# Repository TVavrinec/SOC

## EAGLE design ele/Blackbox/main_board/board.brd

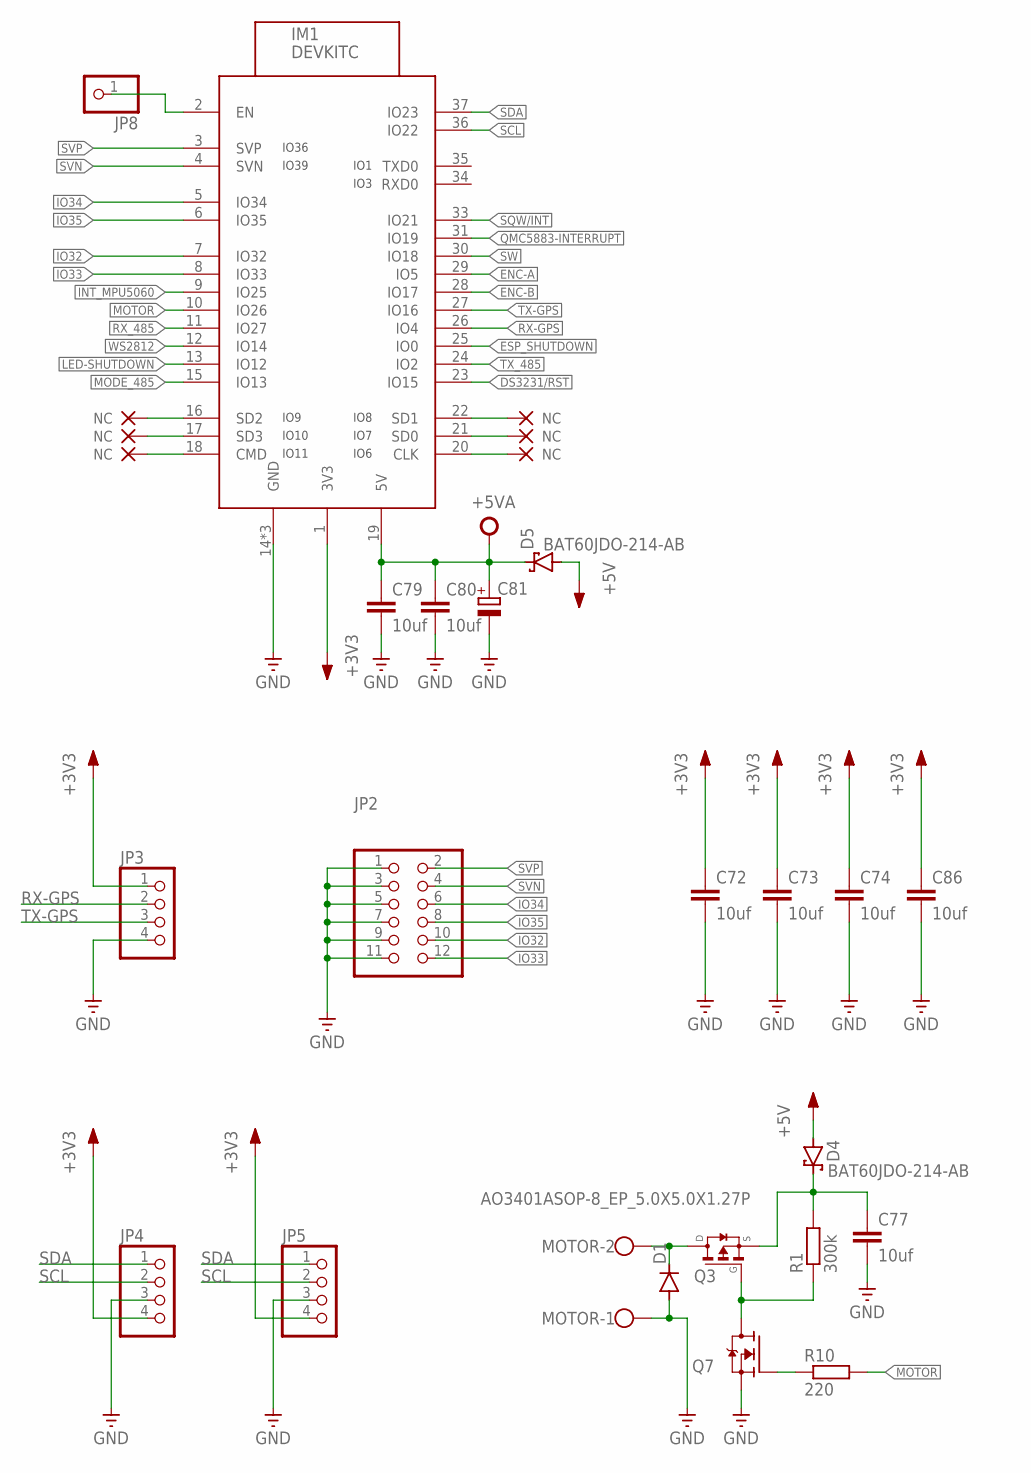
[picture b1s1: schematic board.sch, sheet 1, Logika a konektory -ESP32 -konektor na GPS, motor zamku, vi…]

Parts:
C72, C73, C74, C77, C79, C80, C86: 10uf; C0805
C81: CPOL-EU; E5-10,5-H
D1: DIODE-DO214BA; DO214BA
D4, D5: BAT60JDO-214-AB; DO214BA
IM1: DEVKITC
JP2: PINHD-2X6; 2X06
JP3, JP4, JP5: PINHD-1X4; 1X04
JP8: PINHD-1X1; 1X01
MOTOR: W237-102
Q3: AO3401ASOP-8_EP_5.0X5.0X1.27P; SOP-8_EP_5.0X5.0X1.27P
Q7: N-MOSFET-SOT23-GSD; SOT23
R1: 300k; R0402
R10: 220; R0402

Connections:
+3V3: C72.1, C73.1, C74.1, C86.1, IM1.1 (3V3), JP3.1, JP4.4, JP5.4; also elsewhere on the board
+5V: D4.A, D5.A; also elsewhere on the board
+5VA: C79.1, C80.1, C81.+, D5.C, IM1.19 (5V); also elsewhere on the board
DS3231/RST: IM1.23 (IO15); also elsewhere on the board
ENC-A: IM1.29 (IO5); also elsewhere on the board
ENC-B: IM1.28 (IO17); also elsewhere on the board
ESP_SHUTDOWN: IM1.25 (IO0); also elsewhere on the board
GND: C72.2, C73.2, C74.2, C77.2, C79.2, C80.2, C81.-, C86.2, D1.A, IM1.14 (GND), IM1.32 (GND), IM1.38 (GND), JP2.1, JP2.3, JP2.5, JP2.7, JP2.9, JP2.11, JP3.4, JP4.3, JP5.3, MOTOR.1, Q7.2 (S); also elsewhere on the board
INT_MPU5060: IM1.9 (IO25); also elsewhere on the board
IO9_NC: IM1.16 (SD2)
IO9_NC1: IM1.20 (CLK)
IO10_NC: IM1.17 (SD3)
IO10_NC1: IM1.21 (SD0)
IO11_NC: IM1.18 (CMD)
IO11_NC1: IM1.22 (SD1)
IO32: IM1.7 (IO32), JP2.10
IO33: IM1.8 (IO33), JP2.12
IO34: IM1.5 (IO34), JP2.6
IO35: IM1.6 (IO35), JP2.8
LED-SHUTDOWN: IM1.13 (IO12); also elsewhere on the board
MODE_485: IM1.15 (IO13); also elsewhere on the board
MOTOR: IM1.10 (IO26), R10.2
unnamed: IM1.2 (EN), JP8.1
unnamed: D1.C, MOTOR.2, Q3.5 (D), Q3.6 (D), Q3.7 (D), Q3.8 (D), Q3.9 (D)
unnamed: Q3.4 (G), Q7.3 (D), R1.1
unnamed: Q7.1 (G), R10.1
unnamed: C77.1, D4.C, Q3.1 (S), Q3.2 (S), Q3.3 (S), R1.2
QMC5883-INTERRUPT: IM1.31 (IO19); also elsewhere on the board
RX-GPS: IM1.26 (IO4), JP3.2
RX_485: IM1.11 (IO27); also elsewhere on the board
SCL: IM1.36 (IO22), JP4.2, JP5.2; also elsewhere on the board
SDA: IM1.37 (IO23), JP4.1, JP5.1; also elsewhere on the board
SQW/INT: IM1.33 (IO21); also elsewhere on the board
SVN: IM1.4 (SVN), JP2.4
SVP: IM1.3 (SVP), JP2.2
SW: IM1.30 (IO18); also elsewhere on the board
TX-GPS: IM1.27 (IO16), JP3.3
TX_485: IM1.24 (IO2); also elsewhere on the board
WS2812: IM1.12 (IO14); also elsewhere on the board

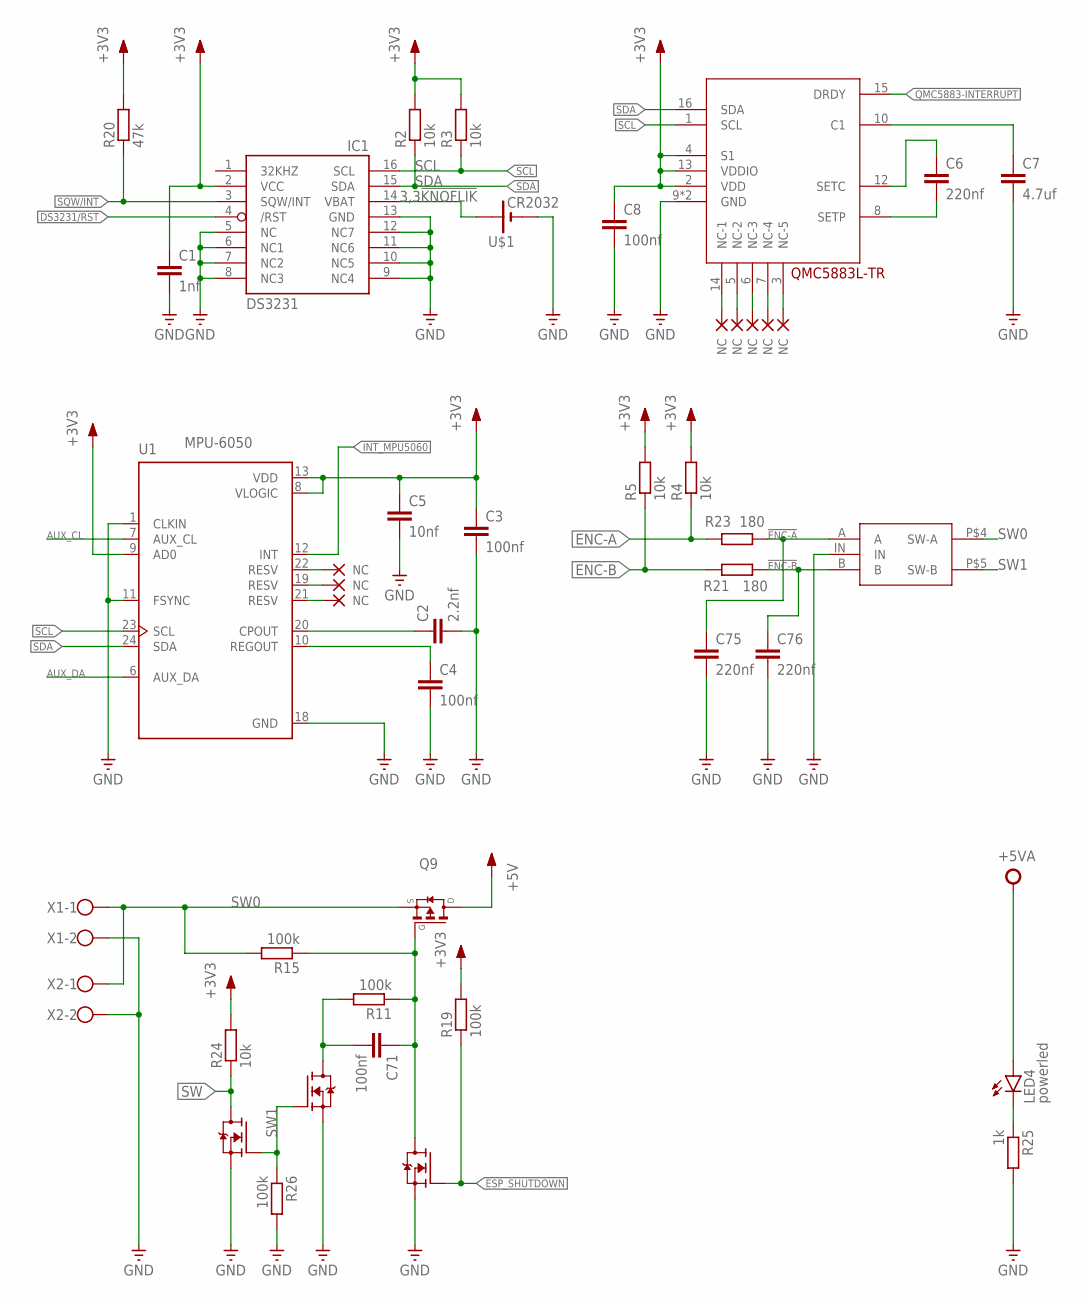
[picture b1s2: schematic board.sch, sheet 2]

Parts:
C1: 1nf; C0402
C2: 2.2nf; C0402
C3: 100nf; C0402
C4, C8, C71: 100nf; C0402P
C5: 10nf; C0402
C6, C75, C76: 220nf; C0402
C7: 4.7uf; C0805
IC1: DS3231/SO; SO16W
IC2: QMC5883L-TR; QMC5882L-TR
LED4: powerled; SML0603
Q4, Q5, Q11: N-MOSFET-SOT23-GSD; SOT23
Q9: AO3401ASOP-8_EP_5.0X5.0X1.27P; SOP-8_EP_5.0X5.0X1.27P
R2, R3, R4, R5, R24: 10k; R0402
R11, R15, R19, R26: 100k; R0402
R20: 47k; R0402
R21, R23: 180; R0402
R25: 1k; R0402
U1: MPU-6050; QFN50P400X400X95-24N
U$1: CR2032; CH075
U$62: EC11-1S
X1, X2: W237-102

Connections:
3,3!KNOFLIK: IC1.14 (VBAT), U$1.+
!ENC-A: C75.1, R23.1, U$62.A
!ENC-B: C76.1, R21.1, U$62.B
+3V3: C1.1, C3.1, C5.1, C8.1, IC1.2 (VCC), IC2.2 (VDD), IC2.4 (S1), IC2.13 (VDDIO), R2.2, R3.2, R4.2, R5.2, R19.2, R20.2, R24.2, U1.8 (VLOGIC), U1.9 (AD0), U1.13 (VDD); also elsewhere on the board
+5V: Q9.5 (D), Q9.6 (D), Q9.7 (D), Q9.8 (D), Q9.9 (D); also elsewhere on the board
+5VA: LED4.A; also elsewhere on the board
AUX_CL: U1.7 (AUX_CL)
AUX_DA: U1.6 (AUX_DA)
DS3231/RST: IC1.4 (/RST); also elsewhere on the board
ENC-A: R4.1, R23.2; also elsewhere on the board
ENC-B: R5.1, R21.2; also elsewhere on the board
ESP_SHUTDOWN: Q5.1 (G), R19.1; also elsewhere on the board
GND: C1.2, C2.2, C3.2, C4.2, C5.2, C7.2, C8.2, C75.2, C76.2, IC1.5 (NC), IC1.6 (NC1), IC1.7 (NC2), IC1.8 (NC3), IC1.9 (NC4), IC1.10 (NC5), IC1.11 (NC6), IC1.12 (NC7), IC1.13 (GND), IC2.9 (GND), IC2.11 (GND), Q4.2 (S), Q5.2 (S), Q11.2 (S), R25.2, R26.2, U1.1 (CLKIN), U1.11 (FSYNC), U1.18 (GND), U$1.-, U$62.IN, X1.2, X2.2; also elsewhere on the board
INT_MPU5060: U1.12 (INT); also elsewhere on the board
IO9_NC2: IC2.5 (NC-2)
IO9_NC3: IC2.14 (NC-1)
IO9_NC4: U1.19 (RESV)
IO9_NC5: U1.21 (RESV)
IO9_NC6: IC2.3 (NC-5)
IO9_NC7: IC2.7 (NC-4)
IO10_NC2: IC2.6 (NC-3)
IO10_NC4: U1.22 (RESV)
LED4: LED4.C, R25.1
unnamed: C2.1, U1.20 (CPOUT)
unnamed: C71.2, Q4.3 (D), R11.2
unnamed: C4.1, U1.10 (REGOUT)
unnamed: C71.1, Q5.3 (D), Q9.4 (G), R11.1, R15.1
unnamed: C6.1, IC2.12 (SETC)
unnamed: C6.2, IC2.8 (SETP)
unnamed: C7.1, IC2.10 (C1)
QMC5883-INTERRUPT: IC2.15 (DRDY); also elsewhere on the board
SCL: IC1.16 (SCL), IC2.1 (SCL), R3.1, U1.23 (SCL); also elsewhere on the board
SDA: IC1.15 (SDA), IC2.16 (SDA), R2.1, U1.24 (SDA); also elsewhere on the board
SQW/INT: IC1.3 (SQW/INT), R20.1; also elsewhere on the board
SW: Q11.3 (D), R24.1; also elsewhere on the board
SW0: Q9.1 (S), Q9.2 (S), Q9.3 (S), R15.2, U$62.P$4 (SW-A), X1.1, X2.1
SW1: Q4.1 (G), Q11.1 (G), R26.1, U$62.P$5 (SW-B)

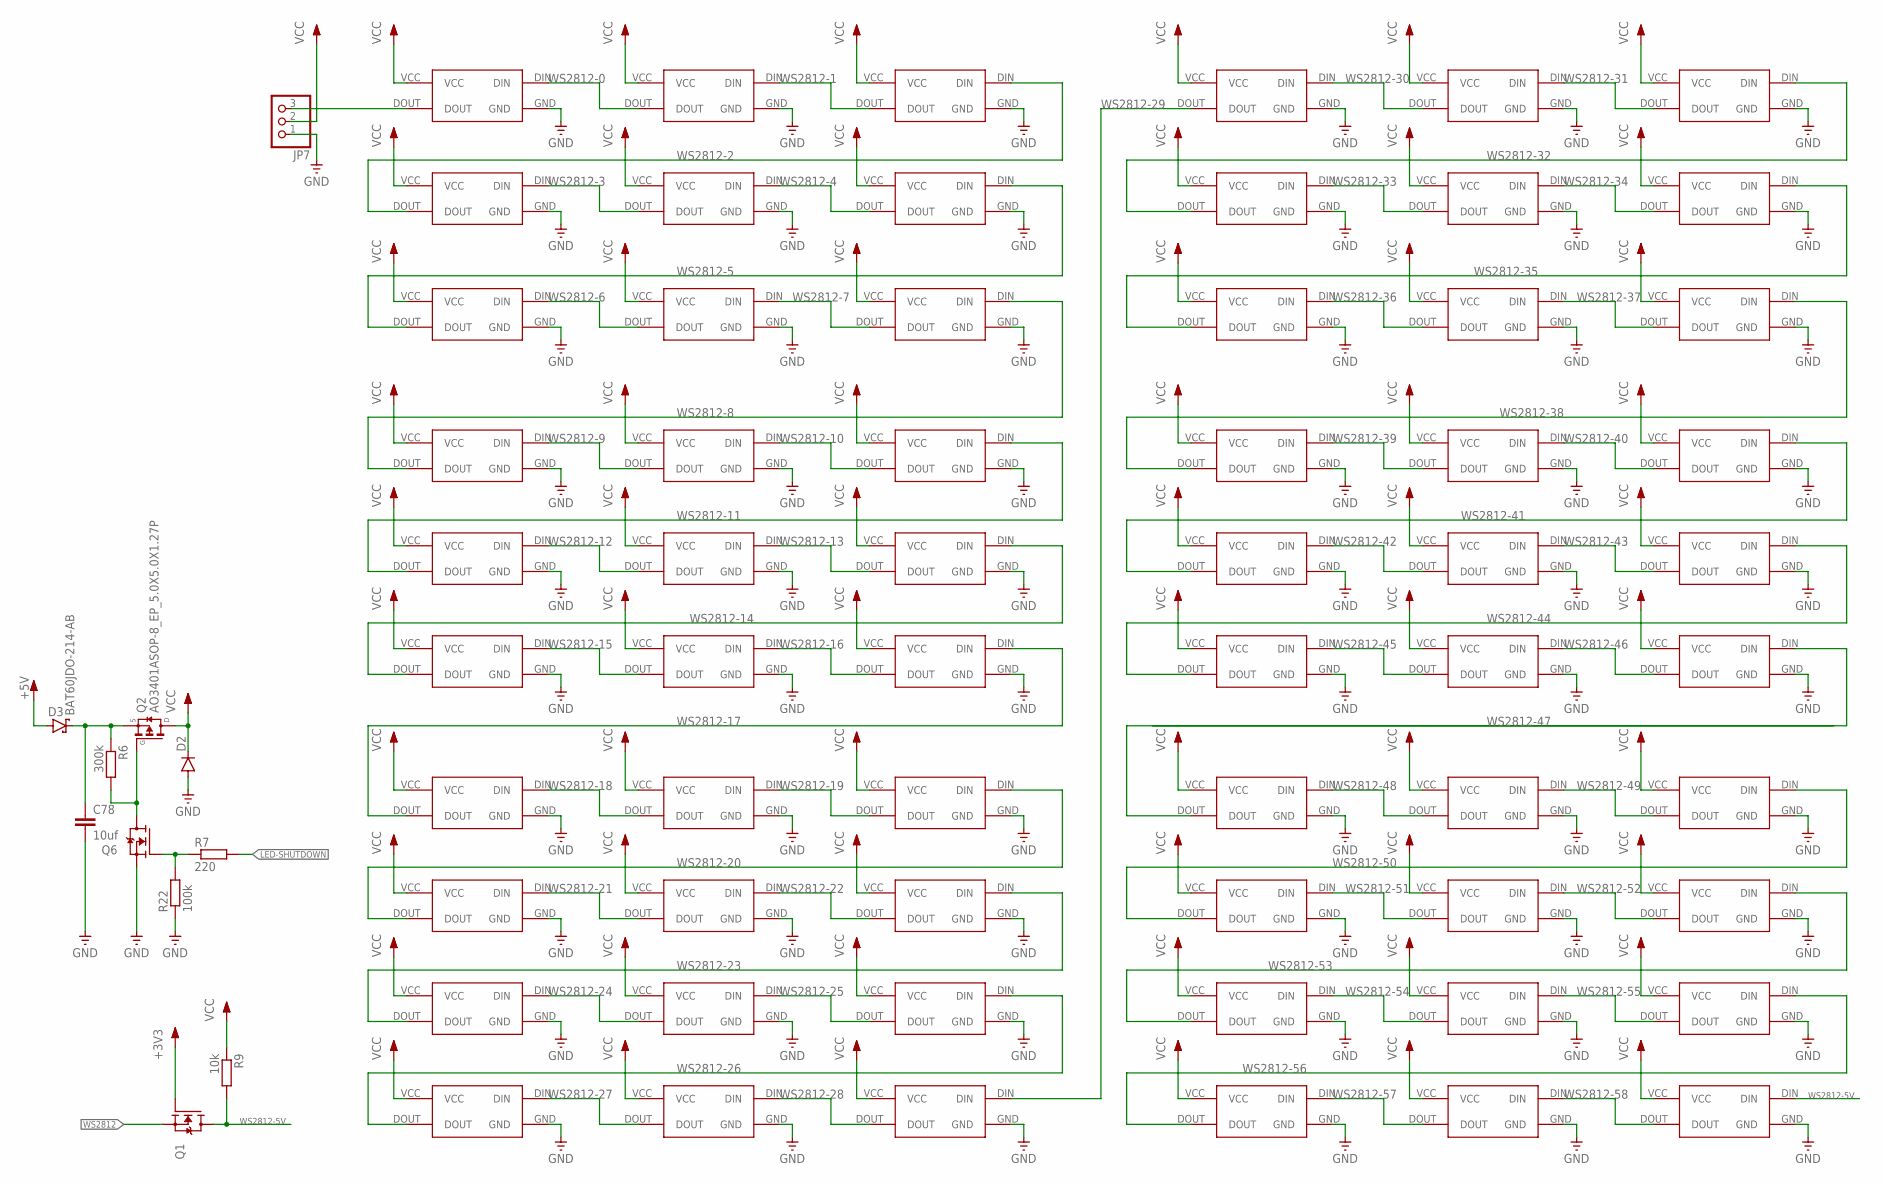
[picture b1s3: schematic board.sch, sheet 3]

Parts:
C78: 10uf; C0805
D2: DIODE-DO214BA; DO214BA
D3: BAT60JDO-214-AB; DO214BA
JP7: PINHD-1X3; 1X03
Q1, Q6: N-MOSFET-SOT23-GSD; SOT23
Q2: AO3401ASOP-8_EP_5.0X5.0X1.27P; SOP-8_EP_5.0X5.0X1.27P
R6: 300k; R0402
R7: 220; R0402
R9: 10k; R0402
R22: 100k; R0402
U$2, U$3, U$4, U$5, U$6, U$7, U$8, U$9, U$10, U$11, U$12, U$13, U$14, U$15, U$16, U$17, U$18, U$19, U$20, U$21, U$22, U$23, U$24, U$25, U$26, U$27, U$28, U$29, U$30, U$31, U$32, U$33, U$34, U$35, U$36, U$37, U$38, U$39, U$40, U$41, U$42, U$43, U$44, U$45, U$46, U$47, U$48, U$49, U$50, U$51, U$52, U$53, U$54, U$55, U$56, U$57, U$58, U$59, U$60, U$61: WS2812; WS2812B-MINI

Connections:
+3V3: Q1.1 (G); also elsewhere on the board
+5V: D3.A; also elsewhere on the board
GND: C78.2, D2.A, JP7.1, Q6.2 (S), R22.1, U$2.GND, U$3.GND, U$4.GND, U$5.GND, U$6.GND, U$7.GND, U$8.GND, U$9.GND, U$10.GND, U$11.GND, U$12.GND, U$13.GND, U$14.GND, U$15.GND, U$16.GND, U$17.GND, U$18.GND, U$19.GND, U$20.GND, U$21.GND, U$22.GND, U$23.GND, U$24.GND, U$25.GND, U$26.GND, U$27.GND, U$28.GND, U$29.GND, U$30.GND, U$31.GND, U$32.GND, U$33.GND, U$34.GND, U$35.GND, U$36.GND, U$37.GND, U$38.GND, U$39.GND, U$40.GND, U$41.GND, U$42.GND, U$43.GND, U$44.GND, U$45.GND, U$46.GND, U$47.GND, U$48.GND, U$49.GND, U$50.GND, U$51.GND, U$52.GND, U$53.GND, U$54.GND, U$55.GND, U$56.GND, U$57.GND, U$58.GND, U$59.GND, U$60.GND, U$61.GND; also elsewhere on the board
LED-SHUTDOWN: R7.2; also elsewhere on the board
unnamed: C78.1, D3.C, Q2.1 (S), Q2.2 (S), Q2.3 (S), R6.1
unnamed: JP7.3, U$2.DOUT
unnamed: U$49.DIN, U$50.DOUT
unnamed: Q2.4 (G), Q6.3 (D), R6.2
unnamed: Q6.1 (G), R7.1, R22.2
VCC: D2.C, JP7.2, Q2.5 (D), Q2.6 (D), Q2.7 (D), Q2.8 (D), Q2.9 (D), R9.1, U$2.VCC, U$3.VCC, U$4.VCC, U$5.VCC, U$6.VCC, U$7.VCC, U$8.VCC, U$9.VCC, U$10.VCC, U$11.VCC, U$12.VCC, U$13.VCC, U$14.VCC, U$15.VCC, U$16.VCC, U$17.VCC, U$18.VCC, U$19.VCC, U$20.VCC, U$21.VCC, U$22.VCC, U$23.VCC, U$24.VCC, U$25.VCC, U$26.VCC, U$27.VCC, U$28.VCC, U$29.VCC, U$30.VCC, U$31.VCC, U$32.VCC, U$33.VCC, U$34.VCC, U$35.VCC, U$36.VCC, U$37.VCC, U$38.VCC, U$39.VCC, U$40.VCC, U$41.VCC, U$42.VCC, U$43.VCC, U$44.VCC, U$45.VCC, U$46.VCC, U$47.VCC, U$48.VCC, U$49.VCC, U$50.VCC, U$51.VCC, U$52.VCC, U$53.VCC, U$54.VCC, U$55.VCC, U$56.VCC, U$57.VCC, U$58.VCC, U$59.VCC, U$60.VCC, U$61.VCC; also elsewhere on the board
WS2812: Q1.2 (S); also elsewhere on the board
WS2812-0: U$2.DIN, U$3.DOUT
WS2812-1: U$3.DIN, U$4.DOUT
WS2812-2: U$4.DIN, U$5.DOUT
WS2812-3: U$5.DIN, U$6.DOUT
WS2812-4: U$6.DIN, U$7.DOUT
WS2812-5: U$7.DIN, U$8.DOUT
WS2812-5V: Q1.3 (D), R9.2, U$61.DIN
WS2812-6: U$8.DIN, U$9.DOUT
WS2812-7: U$9.DIN, U$10.DOUT
WS2812-8: U$10.DIN, U$11.DOUT
WS2812-9: U$11.DIN, U$12.DOUT
WS2812-10: U$12.DIN, U$13.DOUT
WS2812-11: U$13.DIN, U$14.DOUT
WS2812-12: U$14.DIN, U$15.DOUT
WS2812-13: U$15.DIN, U$16.DOUT
WS2812-14: U$16.DIN, U$17.DOUT
WS2812-15: U$17.DIN, U$18.DOUT
WS2812-16: U$18.DIN, U$19.DOUT
WS2812-17: U$19.DIN, U$20.DOUT
WS2812-18: U$20.DIN, U$21.DOUT
WS2812-19: U$21.DIN, U$22.DOUT
WS2812-20: U$22.DIN, U$23.DOUT
WS2812-21: U$23.DIN, U$24.DOUT
WS2812-22: U$24.DIN, U$25.DOUT
WS2812-23: U$25.DIN, U$26.DOUT
WS2812-24: U$26.DIN, U$27.DOUT
WS2812-25: U$27.DIN, U$28.DOUT
WS2812-26: U$28.DIN, U$29.DOUT
WS2812-27: U$29.DIN, U$30.DOUT
WS2812-28: U$30.DIN, U$31.DOUT
WS2812-29: U$31.DIN, U$32.DOUT
WS2812-30: U$32.DIN, U$33.DOUT
WS2812-31: U$33.DIN, U$34.DOUT
WS2812-32: U$34.DIN, U$35.DOUT
WS2812-33: U$35.DIN, U$36.DOUT
WS2812-34: U$36.DIN, U$37.DOUT
WS2812-35: U$37.DIN, U$38.DOUT
WS2812-36: U$38.DIN, U$39.DOUT
WS2812-37: U$39.DIN, U$40.DOUT
WS2812-38: U$40.DIN, U$41.DOUT
WS2812-39: U$41.DIN, U$42.DOUT
WS2812-40: U$42.DIN, U$43.DOUT
WS2812-41: U$43.DIN, U$44.DOUT
WS2812-42: U$44.DIN, U$45.DOUT
WS2812-43: U$45.DIN, U$46.DOUT
WS2812-44: U$46.DIN, U$47.DOUT
WS2812-45: U$47.DIN, U$48.DOUT
WS2812-46: U$48.DIN, U$49.DOUT
WS2812-48: U$50.DIN, U$51.DOUT
WS2812-49: U$51.DIN, U$52.DOUT
WS2812-50: U$52.DIN, U$53.DOUT
WS2812-51: U$53.DIN, U$54.DOUT
WS2812-52: U$54.DIN, U$55.DOUT
WS2812-53: U$55.DIN, U$56.DOUT
WS2812-54: U$56.DIN, U$57.DOUT
WS2812-55: U$57.DIN, U$58.DOUT
WS2812-56: U$58.DIN, U$59.DOUT
WS2812-57: U$59.DIN, U$60.DOUT
WS2812-58: U$60.DIN, U$61.DOUT

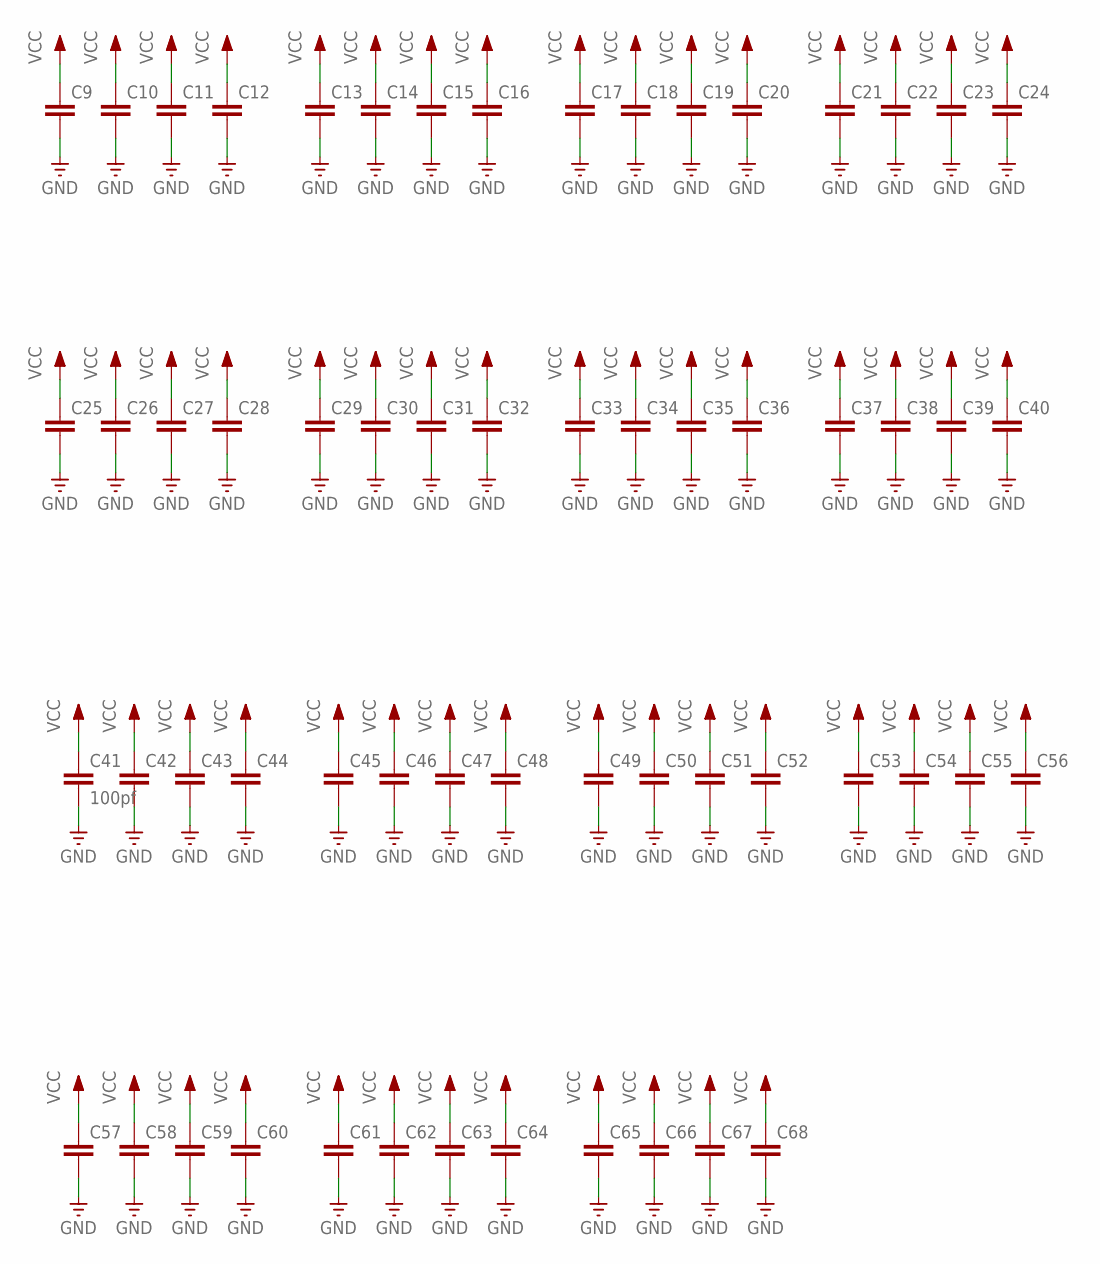
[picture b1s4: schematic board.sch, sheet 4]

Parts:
C9, C10, C11, C12, C13, C14, C15, C16, C17, C18, C19, C20, C21, C22, C23, C24, C25, C26, C27, C28, C29, C30, C31, C32, C33, C34, C35, C36, C37, C38, C39, C40, C42, C43, C44, C45, C46, C47, C48, C49, C50, C51, C52, C53, C54, C55, C56, C57, C58, C59, C60, C61, C62, C63, C64, C65, C66, C67, C68: C-EUC0402; C0402
C41: 100pf; C0402

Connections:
GND: C9.2, C10.2, C11.2, C12.2, C13.2, C14.2, C15.2, C16.2, C17.2, C18.2, C19.2, C20.2, C21.2, C22.2, C23.2, C24.2, C25.2, C26.2, C27.2, C28.2, C29.2, C30.2, C31.2, C32.2, C33.2, C34.2, C35.2, C36.2, C37.2, C38.2, C39.2, C40.2, C41.2, C42.2, C43.2, C44.2, C45.2, C46.2, C47.2, C48.2, C49.2, C50.2, C51.2, C52.2, C53.2, C54.2, C55.2, C56.2, C57.2, C58.2, C59.2, C60.2, C61.2, C62.2, C63.2, C64.2, C65.2, C66.2, C67.2, C68.2; also elsewhere on the board
VCC: C9.1, C10.1, C11.1, C12.1, C13.1, C14.1, C15.1, C16.1, C17.1, C18.1, C19.1, C20.1, C21.1, C22.1, C23.1, C24.1, C25.1, C26.1, C27.1, C28.1, C29.1, C30.1, C31.1, C32.1, C33.1, C34.1, C35.1, C36.1, C37.1, C38.1, C39.1, C40.1, C41.1, C42.1, C43.1, C44.1, C45.1, C46.1, C47.1, C48.1, C49.1, C50.1, C51.1, C52.1, C53.1, C54.1, C55.1, C56.1, C57.1, C58.1, C59.1, C60.1, C61.1, C62.1, C63.1, C64.1, C65.1, C66.1, C67.1, C68.1; also elsewhere on the board

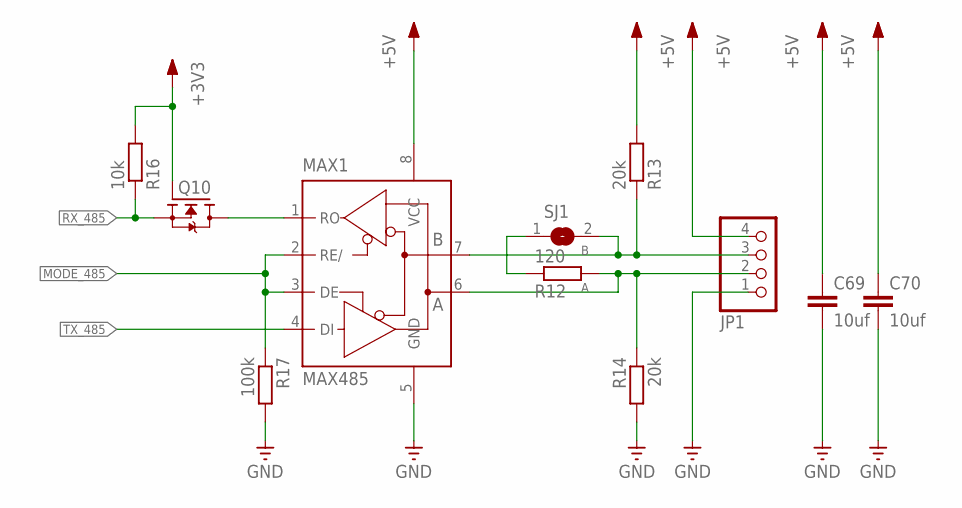
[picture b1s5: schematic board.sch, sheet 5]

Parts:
C69, C70: 10uf; C0805
JP1: PINHD-1X4; 1X04
MAX1: MAX485; SO08
Q10: N-MOSFET-SOT23-GSD; SOT23
R12: 120; R0402
R13, R14: 20k; R0402
R16: 10k; R0402
R17: 100k; R0402
SJ1: SJ

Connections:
+3V3: Q10.1 (G), R16.2; also elsewhere on the board
+5V: C69.1, C70.1, JP1.4, MAX1.8 (VCC), R13.2; also elsewhere on the board
A: JP1.2, MAX1.6 (A), R12.2, R14.1
B: JP1.3, MAX1.7 (B), R13.1, SJ1.2
GND: C69.2, C70.2, JP1.1, MAX1.5 (GND), R14.2, R17.2; also elsewhere on the board
MODE_485: MAX1.2 (RE/), MAX1.3 (DE), R17.1; also elsewhere on the board
unnamed: R12.1, SJ1.1
RX-485-5V: MAX1.1 (RO), Q10.3 (D)
RX_485: Q10.2 (S), R16.1; also elsewhere on the board
TX_485: MAX1.4 (DI); also elsewhere on the board

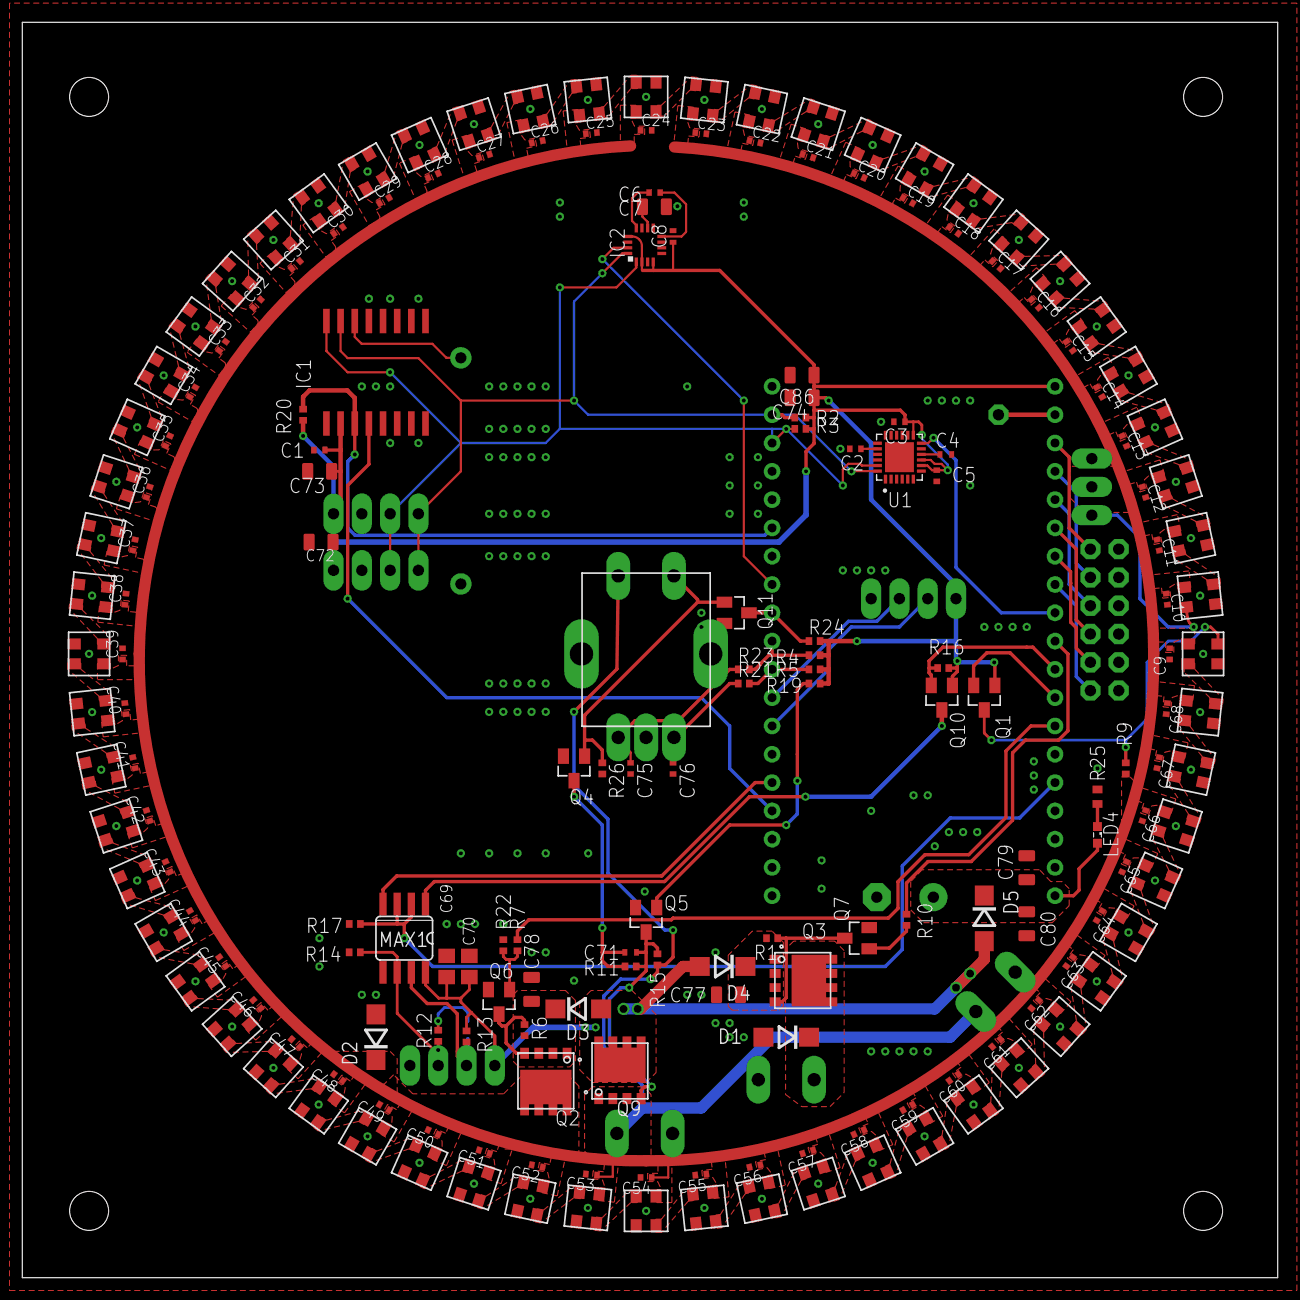
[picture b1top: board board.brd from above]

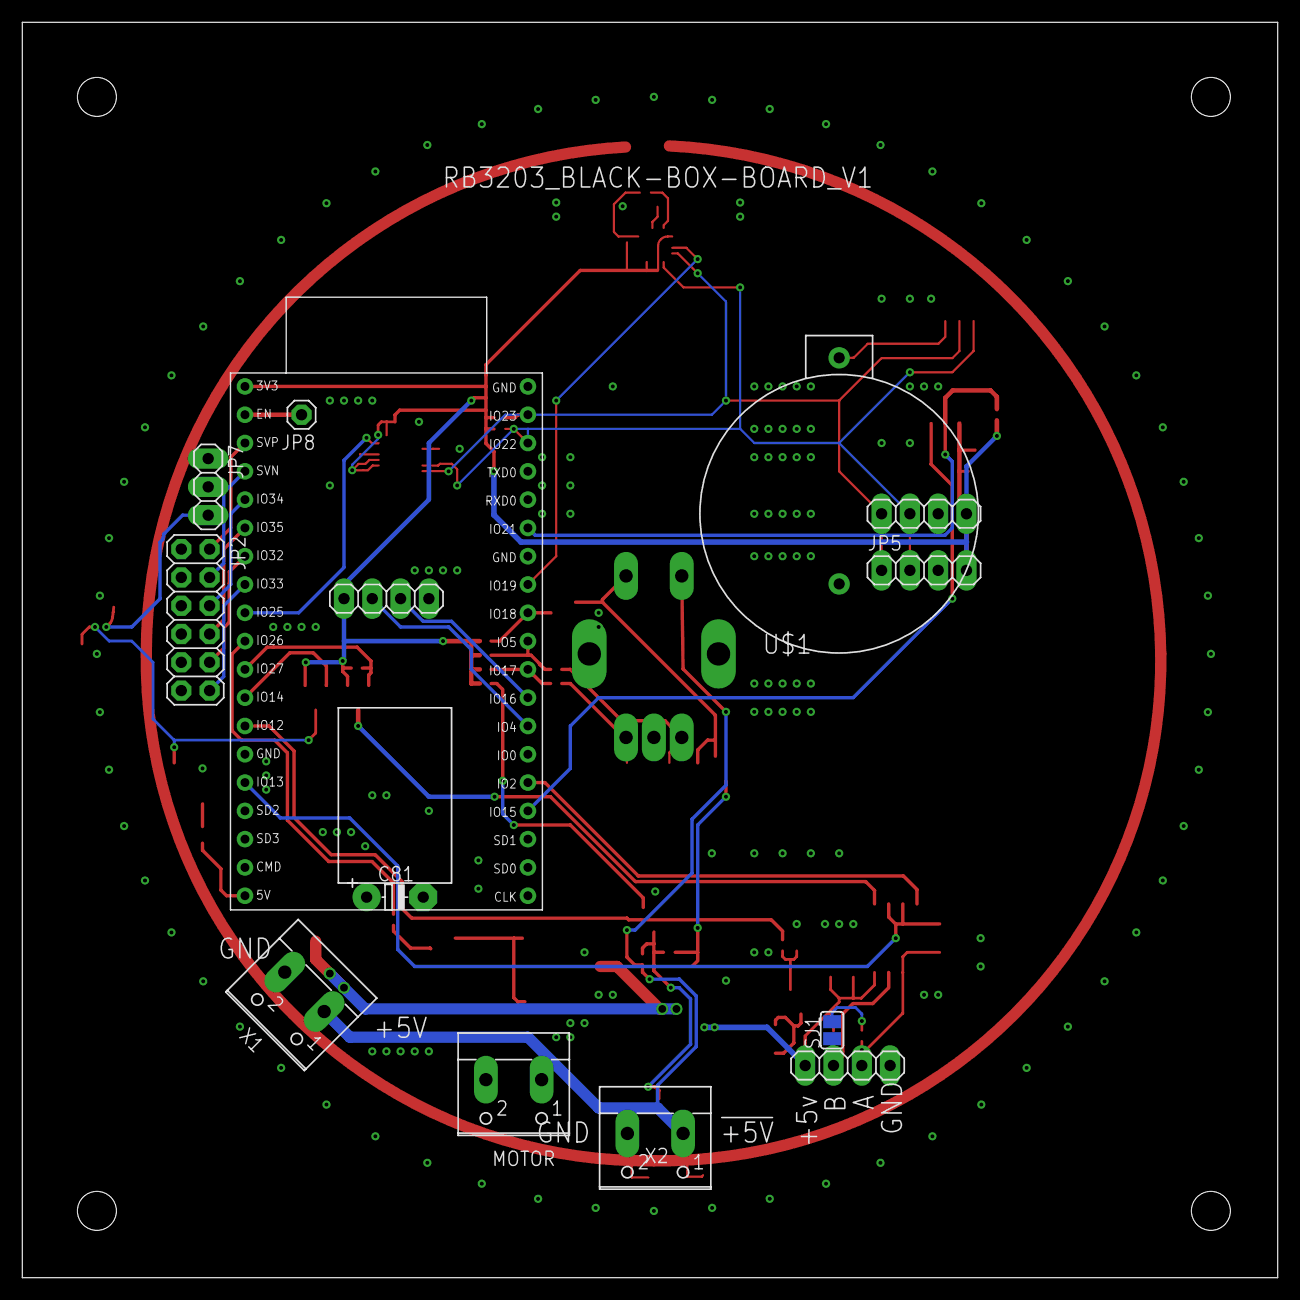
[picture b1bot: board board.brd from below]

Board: 2 copper layers, 112.7 x 112.7 mm, 200 parts (14 on the bottom side), 115 nets.

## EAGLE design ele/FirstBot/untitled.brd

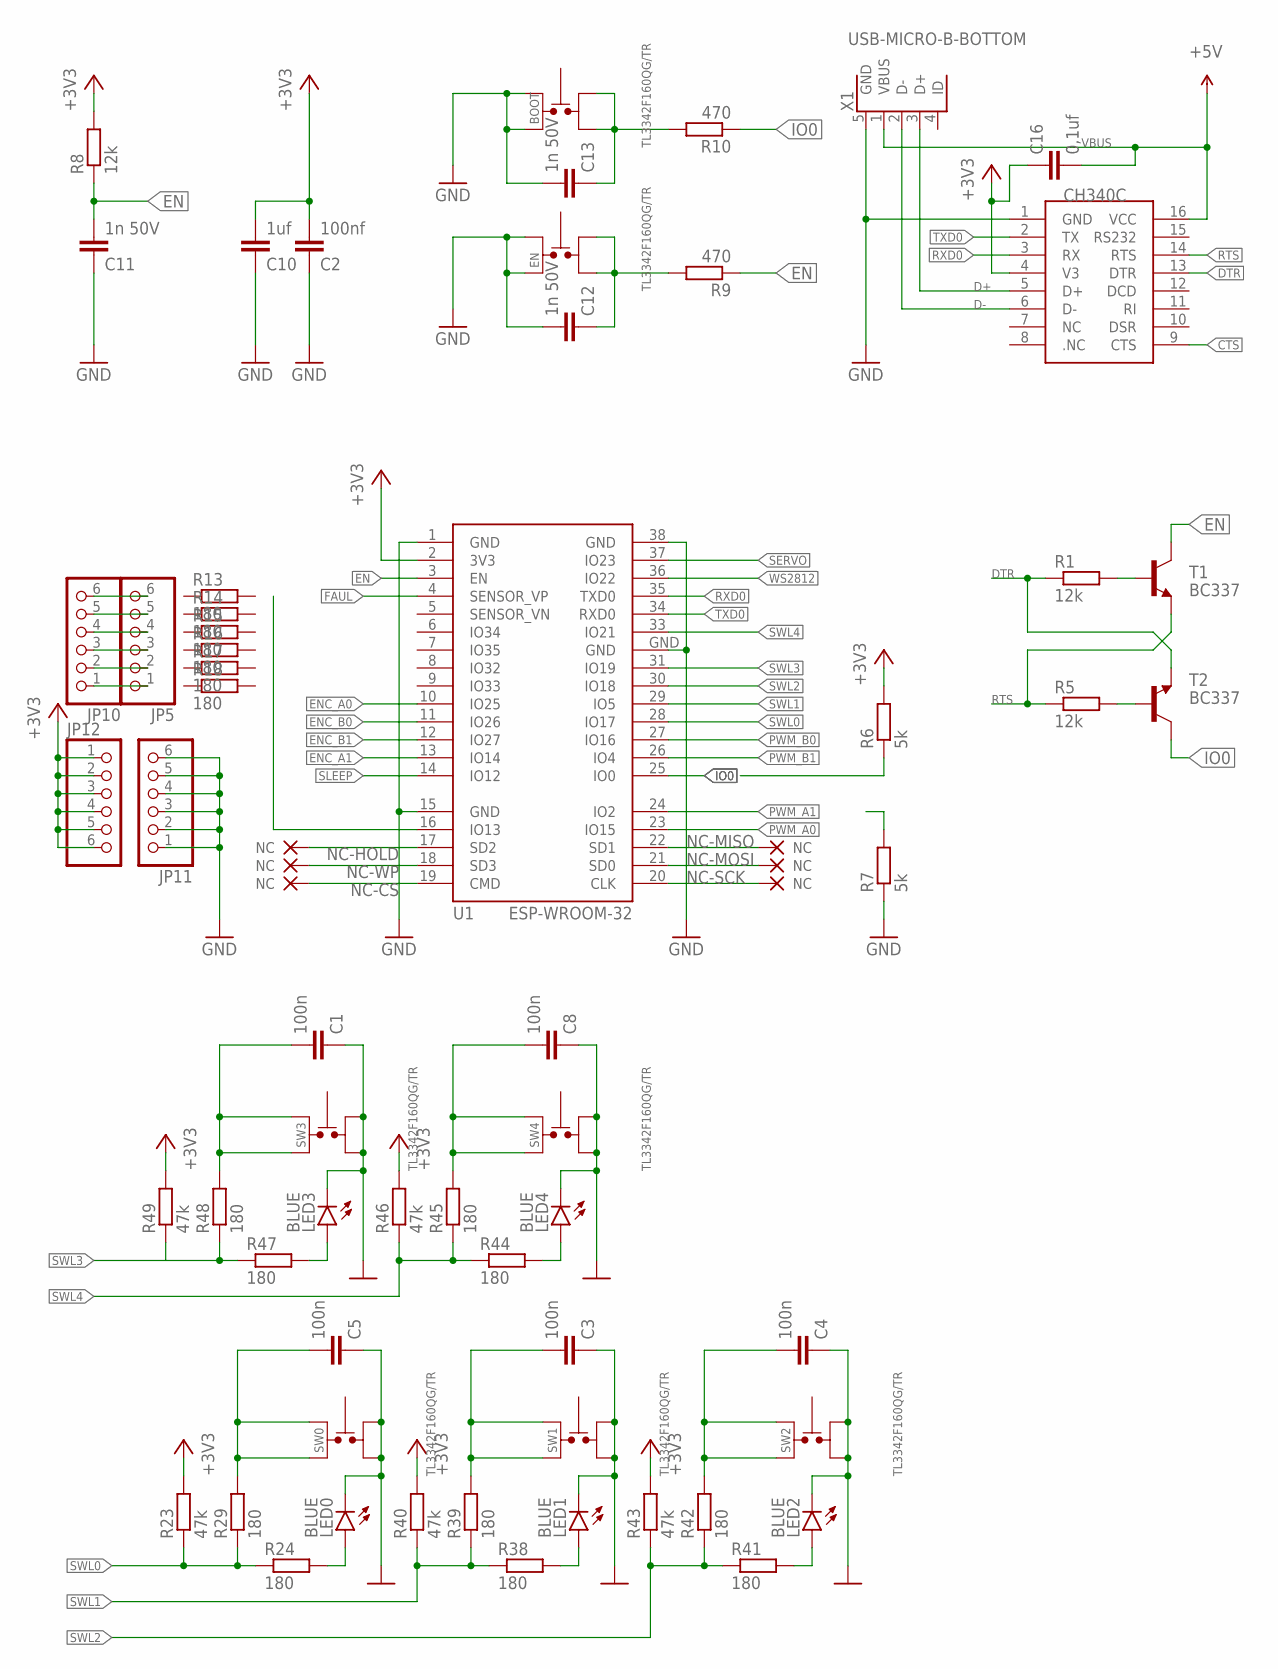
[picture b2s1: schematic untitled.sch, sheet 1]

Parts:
BOOT: TL3342F160QG/TR
C1, C3, C4, C5, C8: 100n; C0402K
C2: 100nf; C0402
C10: 1uf; C0402
C11, C13: 1n 50V; C0402
C12: 1n 50V; C0402K
C16: 0,1uf; C0402
CH1: CH340C; SOIC16
EN: TL3342F160QG/TR
JP5, JP10, JP11, JP12: PINHD-1X6; 1X06
LED0, LED1, LED2, LED3, LED4: BLUE; CHIPLED_1206
R1, R5: 12k; R0603
R6, R7: 5k; R0402
R8: 12k; R0402
R9, R10: 470; R0402
R13, R14, R15, R16, R17, R18, R24, R29, R38, R39, R41, R42, R44, R45, R47, R48: 180; R0402
R23, R40, R43, R46, R49: 47k; R0402
SW0, SW1, SW2, SW3, SW4: TL3342F160QG/TR
T1, T2: BC337; SOT23
U1: ESP-WROOM-32
X1: USB-MICRO-B-BOTTOM; USB-MICRO-B-BOTTOM-MOLEX

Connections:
!DTR_B: R1.2, T1.1 (B)
!RTS_B: R5.2, T2.1 (B)
+3V3: C2.2, C10.2, C16.1, CH1.4 (V3), JP12.1, JP12.2, JP12.3, JP12.4, JP12.5, JP12.6, R6.2, R8.2, R23.2, R40.2, R43.2, R46.2, R49.2, U1.2 (3V3); also elsewhere on the board
CTS: CH1.9 (CTS)
D+: CH1.5 (D+), X1.3 (D+)
D-: CH1.6 (D-), X1.2 (D-)
DTR: CH1.13 (DTR), R1.1, T2.2 (E)
EN: C11.2, R8.1, R9.1, T1.3 (C), U1.3 (EN)
ENC_A0: U1.10 (IO25); also elsewhere on the board
ENC_A1: U1.13 (IO14); also elsewhere on the board
ENC_B0: U1.11 (IO26); also elsewhere on the board
ENC_B1: U1.12 (IO27); also elsewhere on the board
FAUL: U1.4 (SENSOR_VP); also elsewhere on the board
GND: BOOT.3, BOOT.4, C1.1, C2.1, C3.1, C4.1, C5.1, C8.1, C10.1, C11.1, C12.2, C13.2, CH1.1 (GND), EN.3, EN.4, JP11.1, JP11.2, JP11.3, JP11.4, JP11.5, JP11.6, LED0.C, LED1.C, LED2.C, LED3.C, LED4.C, R7.1, SW0.1, SW0.2, SW1.1, SW1.2, SW2.1, SW2.2, SW3.1, SW3.2, SW4.1, SW4.2, U1.1 (GND), U1.15 (GND), U1.38 (GND), U1.GND, X1.5 (GND); also elsewhere on the board
IO0: R6.1, R10.1, T2.3 (C), U1.25 (IO0)
unnamed: C12.1, EN.1, EN.2, R9.2
unnamed: JP5.1, JP10.1
unnamed: JP5.2, JP10.2
unnamed: JP5.3, JP10.3
unnamed: JP5.4, JP10.4
unnamed: JP5.5, JP10.5
unnamed: BOOT.1, BOOT.2, C13.1, R10.2
unnamed: LED0.A, R24.2
unnamed: JP5.6, JP10.6
unnamed: LED2.A, R41.2
unnamed: LED1.A, R38.2
unnamed: LED4.A, R44.2
unnamed: LED3.A, R47.2
NC-CS: U1.19 (CMD)
NC-HOLD: U1.17 (SD2)
NC-MISO: U1.22 (SD1)
NC-MOSI: U1.21 (SD0)
NC-SCK: U1.20 (CLK)
NC-WP: U1.18 (SD3)
PWM_A0: U1.23 (IO15); also elsewhere on the board
PWM_A1: R7.2, U1.24 (IO2); also elsewhere on the board
PWM_B0: U1.27 (IO16); also elsewhere on the board
PWM_B1: U1.26 (IO4); also elsewhere on the board
RTS: CH1.14 (RTS), R5.1, T1.2 (E)
RXD0: CH1.3 (RX), U1.35 (TXD0)
SERVO: U1.37 (IO23); also elsewhere on the board
SLEEP: U1.14 (IO12); also elsewhere on the board
SW0: C5.2, R29.2, SW0.3, SW0.4
SW1: C3.2, R39.2, SW1.3, SW1.4
SW2: C4.2, R42.2, SW2.3, SW2.4
SW3: C1.2, R48.2, SW3.3, SW3.4
SW4: C8.2, R45.2, SW4.3, SW4.4
SWL0: R23.1, R24.1, R29.1, U1.28 (IO17)
SWL1: R38.1, R39.1, R40.1, U1.29 (IO5)
SWL2: R41.1, R42.1, R43.1, U1.30 (IO18)
SWL3: R47.1, R48.1, R49.1, U1.31 (IO19)
SWL4: R44.1, R45.1, R46.1, U1.33 (IO21)
TXD0: CH1.2 (TX), U1.34 (RXD0)
VBUS: C16.2, CH1.16 (VCC), X1.1 (VBUS)
WS2812: U1.36 (IO22); also elsewhere on the board

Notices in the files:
parts and their libraries:
esp32: Creative Commons Attribution-ShareAlike 4.0 International
Copyright (C) PaJa 2001-2011
Copyright (C) PaJa 2011
resistor-array: Copyright (C) 2008, Bob Starr
